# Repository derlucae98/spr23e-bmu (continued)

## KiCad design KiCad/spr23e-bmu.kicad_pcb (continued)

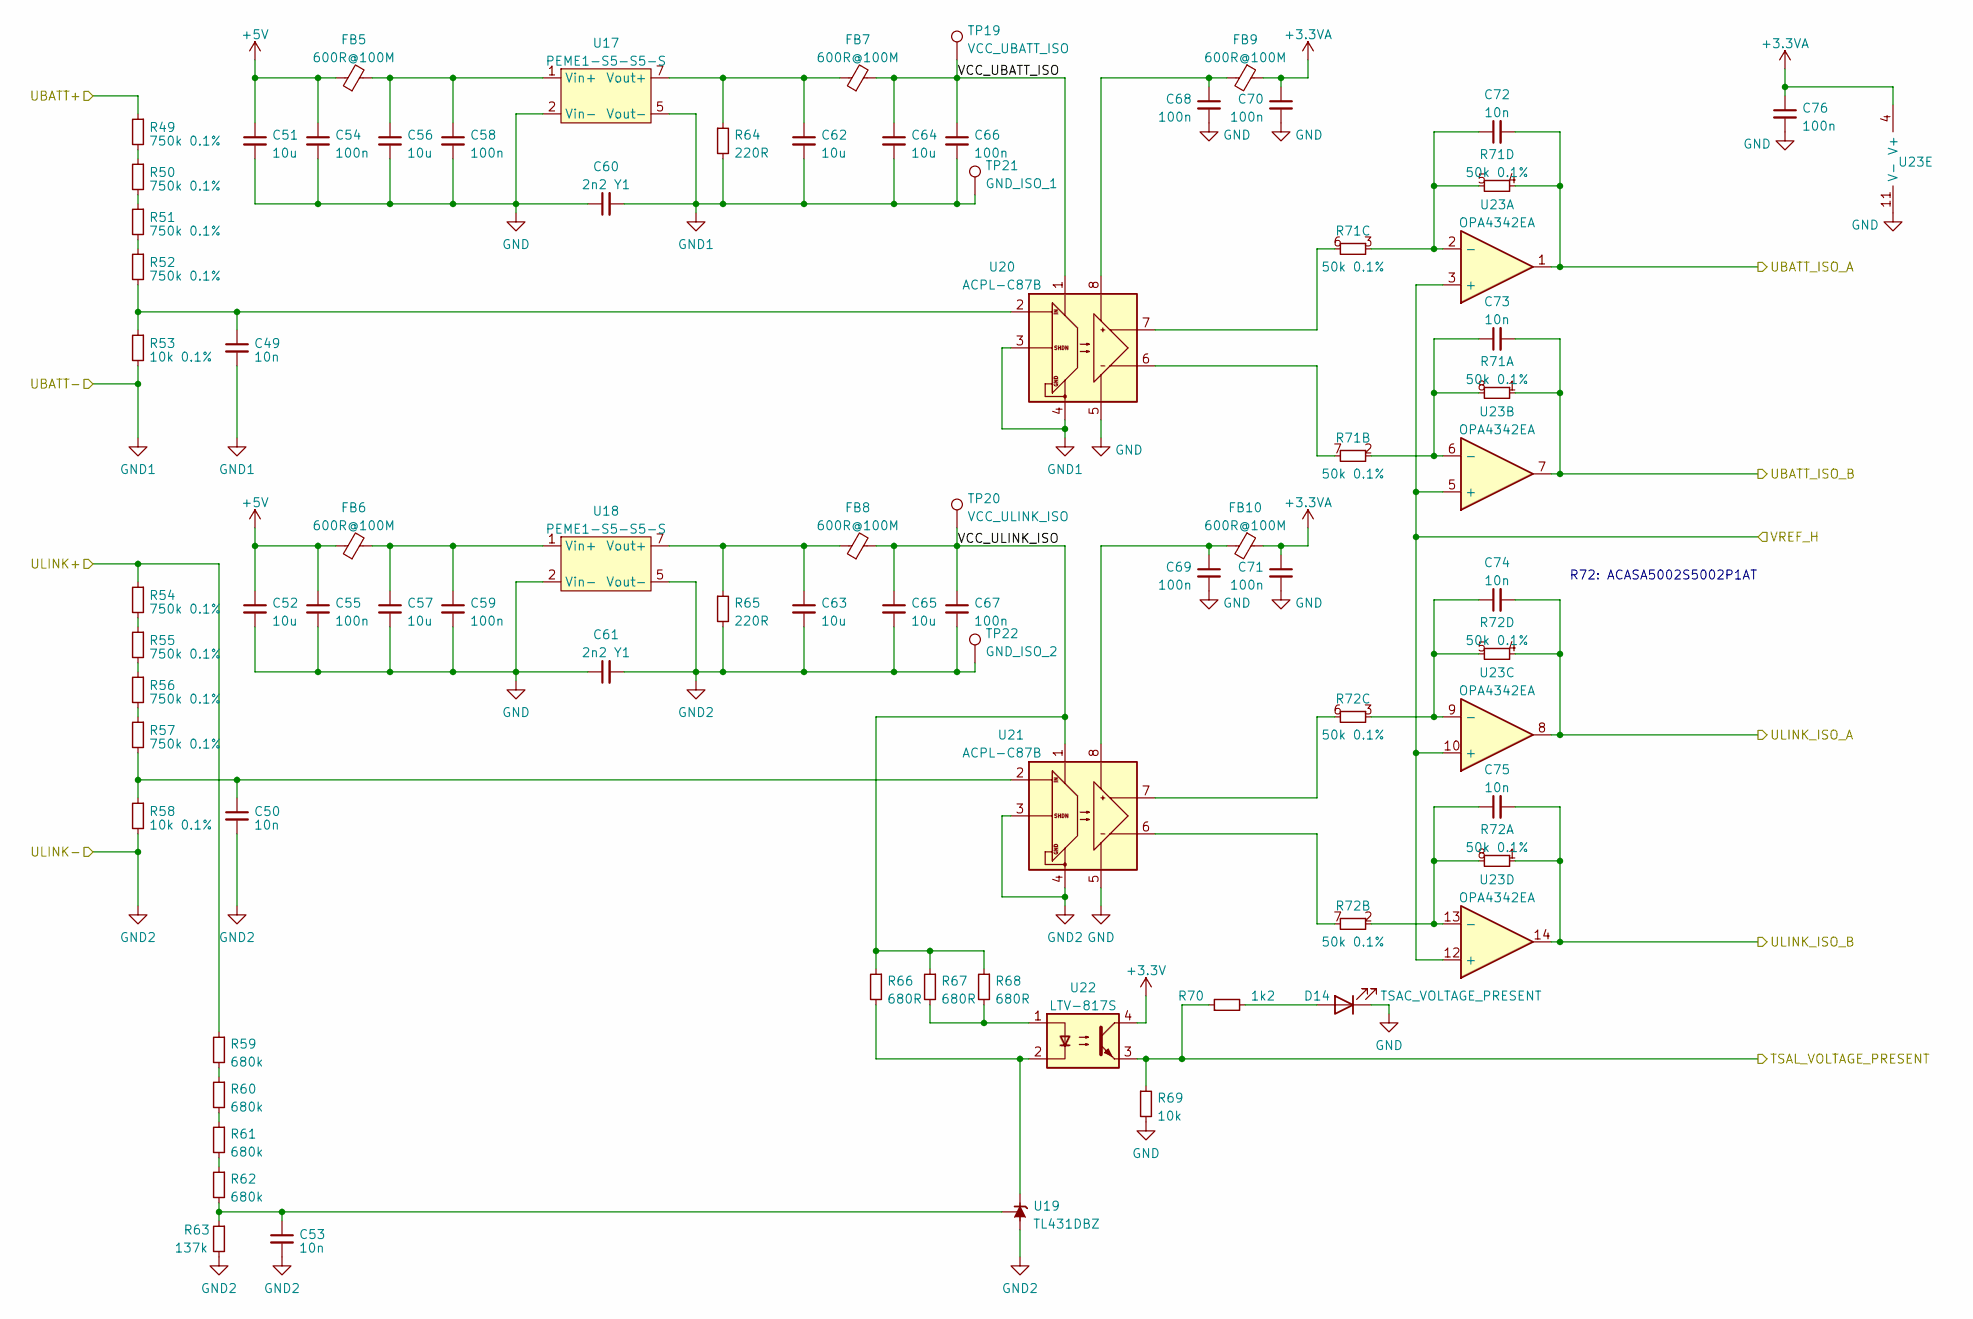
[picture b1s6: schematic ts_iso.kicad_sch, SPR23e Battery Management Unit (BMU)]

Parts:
C49, C50, C53, C72, C73, C74, C75: 10n; C_0603_1608Metric
C51, C52, C56, C57, C62, C63, C64, C65: 10u; C_1206_3216Metric
C54, C55, C58, C59, C66, C67, C68, C69, C70, C71, C76: 100n; C_0603_1608Metric
C60, C61: 2n2 Y1; C_Rect_L13.0mm_W4.0mm_P10.00mm_FKS3_FKP3_MKS4
D14: TSAC_VOLTAGE_PRESENT; LED_0603_1608Metric
FB5, FB6, FB7, FB8, FB9, FB10: 600R@100M; L_0603_1608Metric
R49, R50, R51, R52, R54, R55, R56, R57: 750k 0.1%; R_1206_3216Metric
R53, R58: 10k 0.1%; R_0603_1608Metric
R59, R60, R61, R62: 680k; R_1206_3216Metric
R63: 137k; R_0603_1608Metric
R64, R65: 220R; R_1210_3225Metric
R66, R67, R68: 680R; R_0603_1608Metric
R69: 10k; R_0603_1608Metric
R70: 1k2; R_0603_1608Metric
R71, R72: 50k 0.1%; R_Array_Convex_4x0603
TP19: VCC_UBATT_ISO; TestPoint_Pad_D1.5mm
TP20: VCC_ULINK_ISO; TestPoint_Pad_D1.5mm
TP21: GND_ISO_1; TestPoint_Pad_D1.5mm
TP22: GND_ISO_2; TestPoint_Pad_D1.5mm
U17, U18: PEME1-S5-S5-S; PEME1
U19: TL431DBZ; SOT-23
U20, U21: ACPL-C87B; SSO-8_6.8x5.9mm_P1.27mm_Clearance8mm
U22: LTV-817S; SMDIP-4_W9.53mm
U23: OPA4342EA; TSSOP-14_4.4x5mm_P0.65mm

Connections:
+3.3V: U22.4; also elsewhere on the board
+3.3VA: C70.1, C71.1, C76.1, FB9.1, FB10.1, U23.4 (V+); also elsewhere on the board
+5V: C51.1, C52.1, C54.1, C55.1, FB5.1, FB6.1; also elsewhere on the board
/ADC/UBATT_ISO_A: C72.2, R71.4, U23.1; also elsewhere on the board
/ADC/UBATT_ISO_B: C73.2, R71.1, U23.7; also elsewhere on the board
/ADC/ULINK_ISO_A: C74.2, R72.4, U23.8; also elsewhere on the board
/ADC/ULINK_ISO_B: C75.2, R72.1, U23.14; also elsewhere on the board
/ADC/VREF_H: U23.3 (+), U23.5 (+), U23.10 (+), U23.12 (+); also elsewhere on the board
/AMS-Master/TSAC_VOLTAGE_PRESENT: R69.1, R70.1, U22.3; also elsewhere on the board
/TS_ISO/VCC_UBATT_ISO: C64.1, C66.1, FB7.2, TP19.1, U20.1 (VDD1)
/TS_ISO/VCC_ULINK_ISO: C65.1, C67.1, FB8.2, R66.1, R67.1, R68.1, TP20.1, U21.1 (VDD1)
/UBATT+: R49.1; also elsewhere on the board
/ULINK+: R54.1, R59.1; also elsewhere on the board
GND: C51.2, C52.2, C54.2, C55.2, C56.2, C57.2, C58.2, C59.2, C60.1, C61.1, C68.2, C69.2, C70.2, C71.2, C76.2, D14.1 (K), R69.2, U17.2 (Vin-), U18.2 (Vin-), U20.5 (GND2), U21.5 (GND2), U23.11 (V-); also elsewhere on the board
GND1: C49.2, C60.2, C62.2, C64.2, C66.2, R53.2, R64.2, TP21.1, U17.5 (Vout-), U20.3 (IN-), U20.4 (GND1); also elsewhere on the board
GND2: C50.2, C53.2, C61.2, C63.2, C65.2, C67.2, R58.2, R63.2, R65.2, TP22.1, U18.5 (Vout-), U19.3 (A), U21.3 (IN-), U21.4 (GND1); also elsewhere on the board
unnamed: D14.2 (A), R70.2
unnamed: R49.2, R50.1
unnamed: R50.2, R51.1
unnamed: R51.2, R52.1
unnamed: R54.2, R55.1
unnamed: R55.2, R56.1
unnamed: R56.2, R57.1
unnamed: R59.2, R60.1
unnamed: R60.2, R61.1
unnamed: R61.2, R62.1
unnamed: R67.2, R68.2, U22.1
unnamed: C56.1, C58.1, FB5.2, U17.1 (Vin+)
unnamed: C62.1, FB7.1, R64.1, U17.7 (Vout+)
unnamed: C57.1, C59.1, FB6.2, U18.1 (Vin+)
unnamed: C63.1, FB8.1, R65.1, U18.7 (Vout+)
unnamed: R66.2, U19.1 (K), U22.2
unnamed: C53.1, R62.2, R63.1, U19.2 (REF)
unnamed: C49.1, R52.2, R53.1, U20.2 (IN)
unnamed: R71.6, U20.7 (OUT+)
unnamed: R71.7, U20.6 (OUT-)
unnamed: C68.1, FB9.2, U20.8 (VDD2)
unnamed: C50.1, R57.2, R58.1, U21.2 (IN)
unnamed: R72.6, U21.7 (OUT+)
unnamed: R72.7, U21.6 (OUT-)
unnamed: C69.1, FB10.2, U21.8 (VDD2)
unnamed: C72.1, R71.3, R71.5, U23.2 (-)
unnamed: C73.1, R71.2, R71.8, U23.6 (-)
unnamed: C74.1, R72.3, R72.5, U23.9 (-)
unnamed: C75.1, R72.2, R72.8, U23.13 (-)

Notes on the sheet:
R72: ACASA5002S5002P1AT

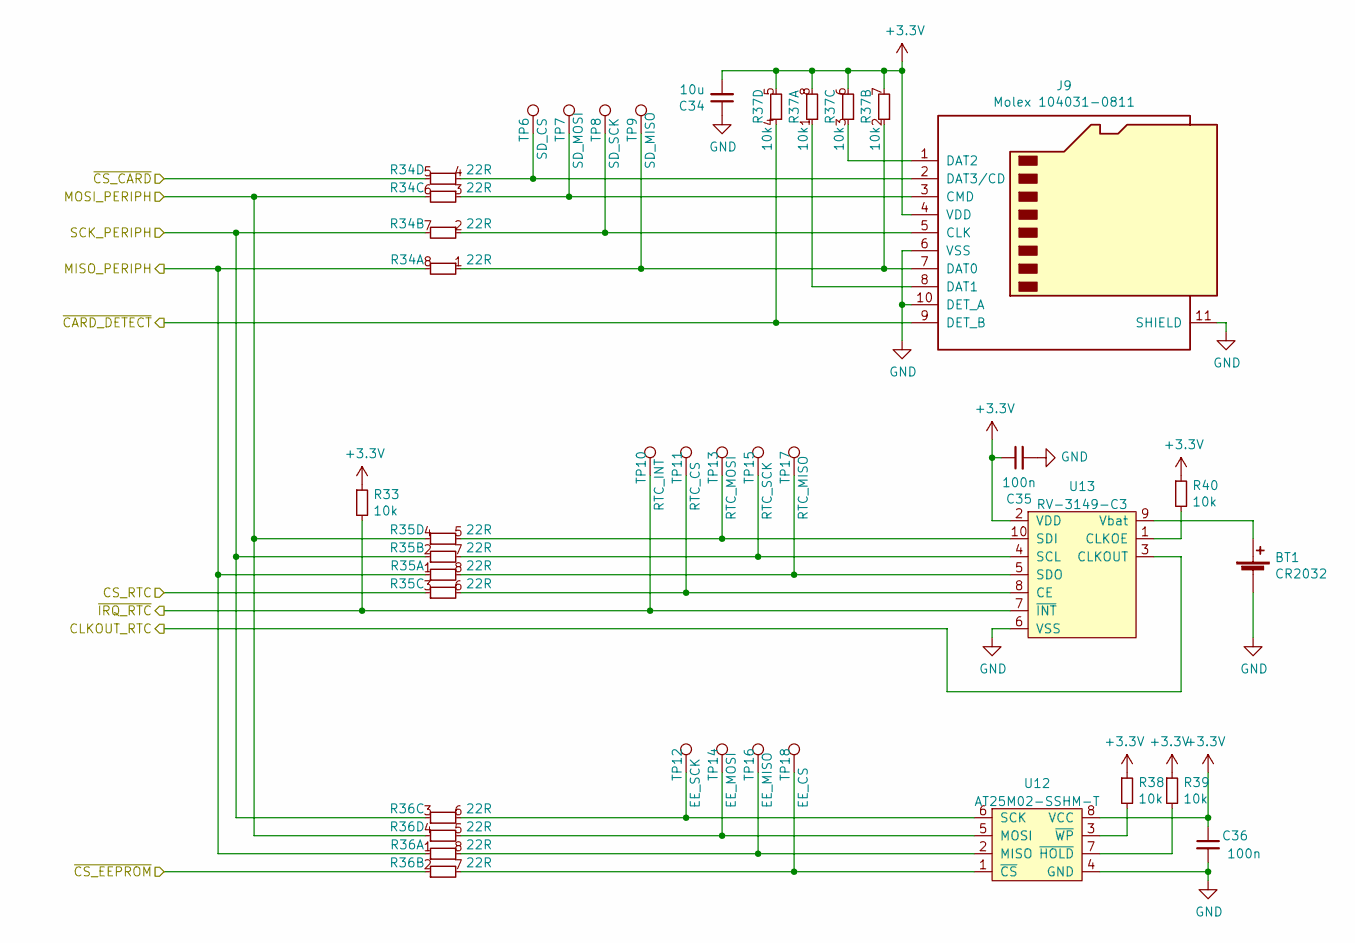
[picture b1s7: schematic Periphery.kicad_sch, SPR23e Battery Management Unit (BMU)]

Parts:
BT1: CR2032; WA-BCPH_79527141
C34: 10u; C_1206_3216Metric
C35, C36: 100n; C_0603_1608Metric
J9: Molex 104031-0811; microSD_HC_Molex_104031-0811
R33, R38, R39, R40: 10k; R_0603_1608Metric
R34, R35, R36: 22R; R_Array_Convex_4x0603
R37: 10k; R_Array_Convex_4x0603
TP6: SD_CS; TestPoint_Pad_D1.5mm
TP7: SD_MOSI; TestPoint_Pad_D1.5mm
TP8: SD_SCK; TestPoint_Pad_D1.5mm
TP9: SD_MISO; TestPoint_Pad_D1.5mm
TP10: RTC_INT; TestPoint_Pad_D1.5mm
TP11: RTC_CS; TestPoint_Pad_D1.5mm
TP12: EE_SCK; TestPoint_Pad_D1.5mm
TP13: RTC_MOSI; TestPoint_Pad_D1.5mm
TP14: EE_MOSI; TestPoint_Pad_D1.5mm
TP15: RTC_SCK; TestPoint_Pad_D1.5mm
TP16: EE_MISO; TestPoint_Pad_D1.5mm
TP17: RTC_MISO; TestPoint_Pad_D1.5mm
TP18: EE_CS; TestPoint_Pad_D1.5mm
U12: AT25M02-SSHM-T; SOIC-8_3.9x4.9mm_P1.27mm
U13: RV-3149-C3; RTC_SMD_MicroCrystal_C3_2.5x3.7mm

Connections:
+3.3V: C34.2, C35.1, C36.1, J9.4 (VDD), R33.1, R37.5, R37.6, R37.7, R37.8, R38.1, R39.1, R40.1, U12.8 (VCC), U13.2 (VDD); also elsewhere on the board
/AMS-Master/CLKOUT_RTC: U13.3 (CLKOUT); also elsewhere on the board
/AMS-Master/CS_RTC: R35.3; also elsewhere on the board
/AMS-Master/SPI2_MISO: R34.8, R35.1, R36.1; also elsewhere on the board
/AMS-Master/SPI2_MOSI: R34.6, R35.4, R36.4; also elsewhere on the board
/AMS-Master/SPI2_SCK: R34.7, R35.2, R36.3; also elsewhere on the board
/AMS-Master/~CARD_DETECT: J9.9 (DET_B), R37.4; also elsewhere on the board
/AMS-Master/~CS_CARD: R34.5; also elsewhere on the board
/AMS-Master/~CS_EEPROM: R36.2; also elsewhere on the board
/AMS-Master/~IRQ_RTC: R33.2, TP10.1, U13.7 (~INT); also elsewhere on the board
GND: BT1.2 (-), C34.1, C35.2, C36.2, J9.6 (VSS), J9.10 (DET_A), J9.11 (SHIELD), U12.4 (GND), U13.6 (VSS); also elsewhere on the board
unnamed: BT1.1 (+), U13.9 (Vbat)
unnamed: J9.5 (CLK), R34.2, TP8.1
unnamed: J9.3 (CMD), R34.3, TP7.1
unnamed: J9.7 (DAT0), R34.1, R37.2, TP9.1
unnamed: J9.8 (DAT1), R37.1
unnamed: J9.1 (DAT2), R37.3
unnamed: J9.2 (DAT3/CD), R34.4, TP6.1
unnamed: R36.8, TP16.1, U12.2 (MISO)
unnamed: R36.5, TP14.1, U12.5 (MOSI)
unnamed: R36.6, TP12.1, U12.6 (SCK)
unnamed: R36.7, TP18.1, U12.1 (~CS)
unnamed: R39.2, U12.7 (~HOLD)
unnamed: R38.2, U12.3 (~WP)
unnamed: R35.6, TP11.1, U13.8 (CE)
unnamed: R40.2, U13.1 (CLKOE)
unnamed: R35.7, TP15.1, U13.4 (SCL)
unnamed: R35.5, TP13.1, U13.10 (SDI)
unnamed: R35.8, TP17.1, U13.5 (SDO)

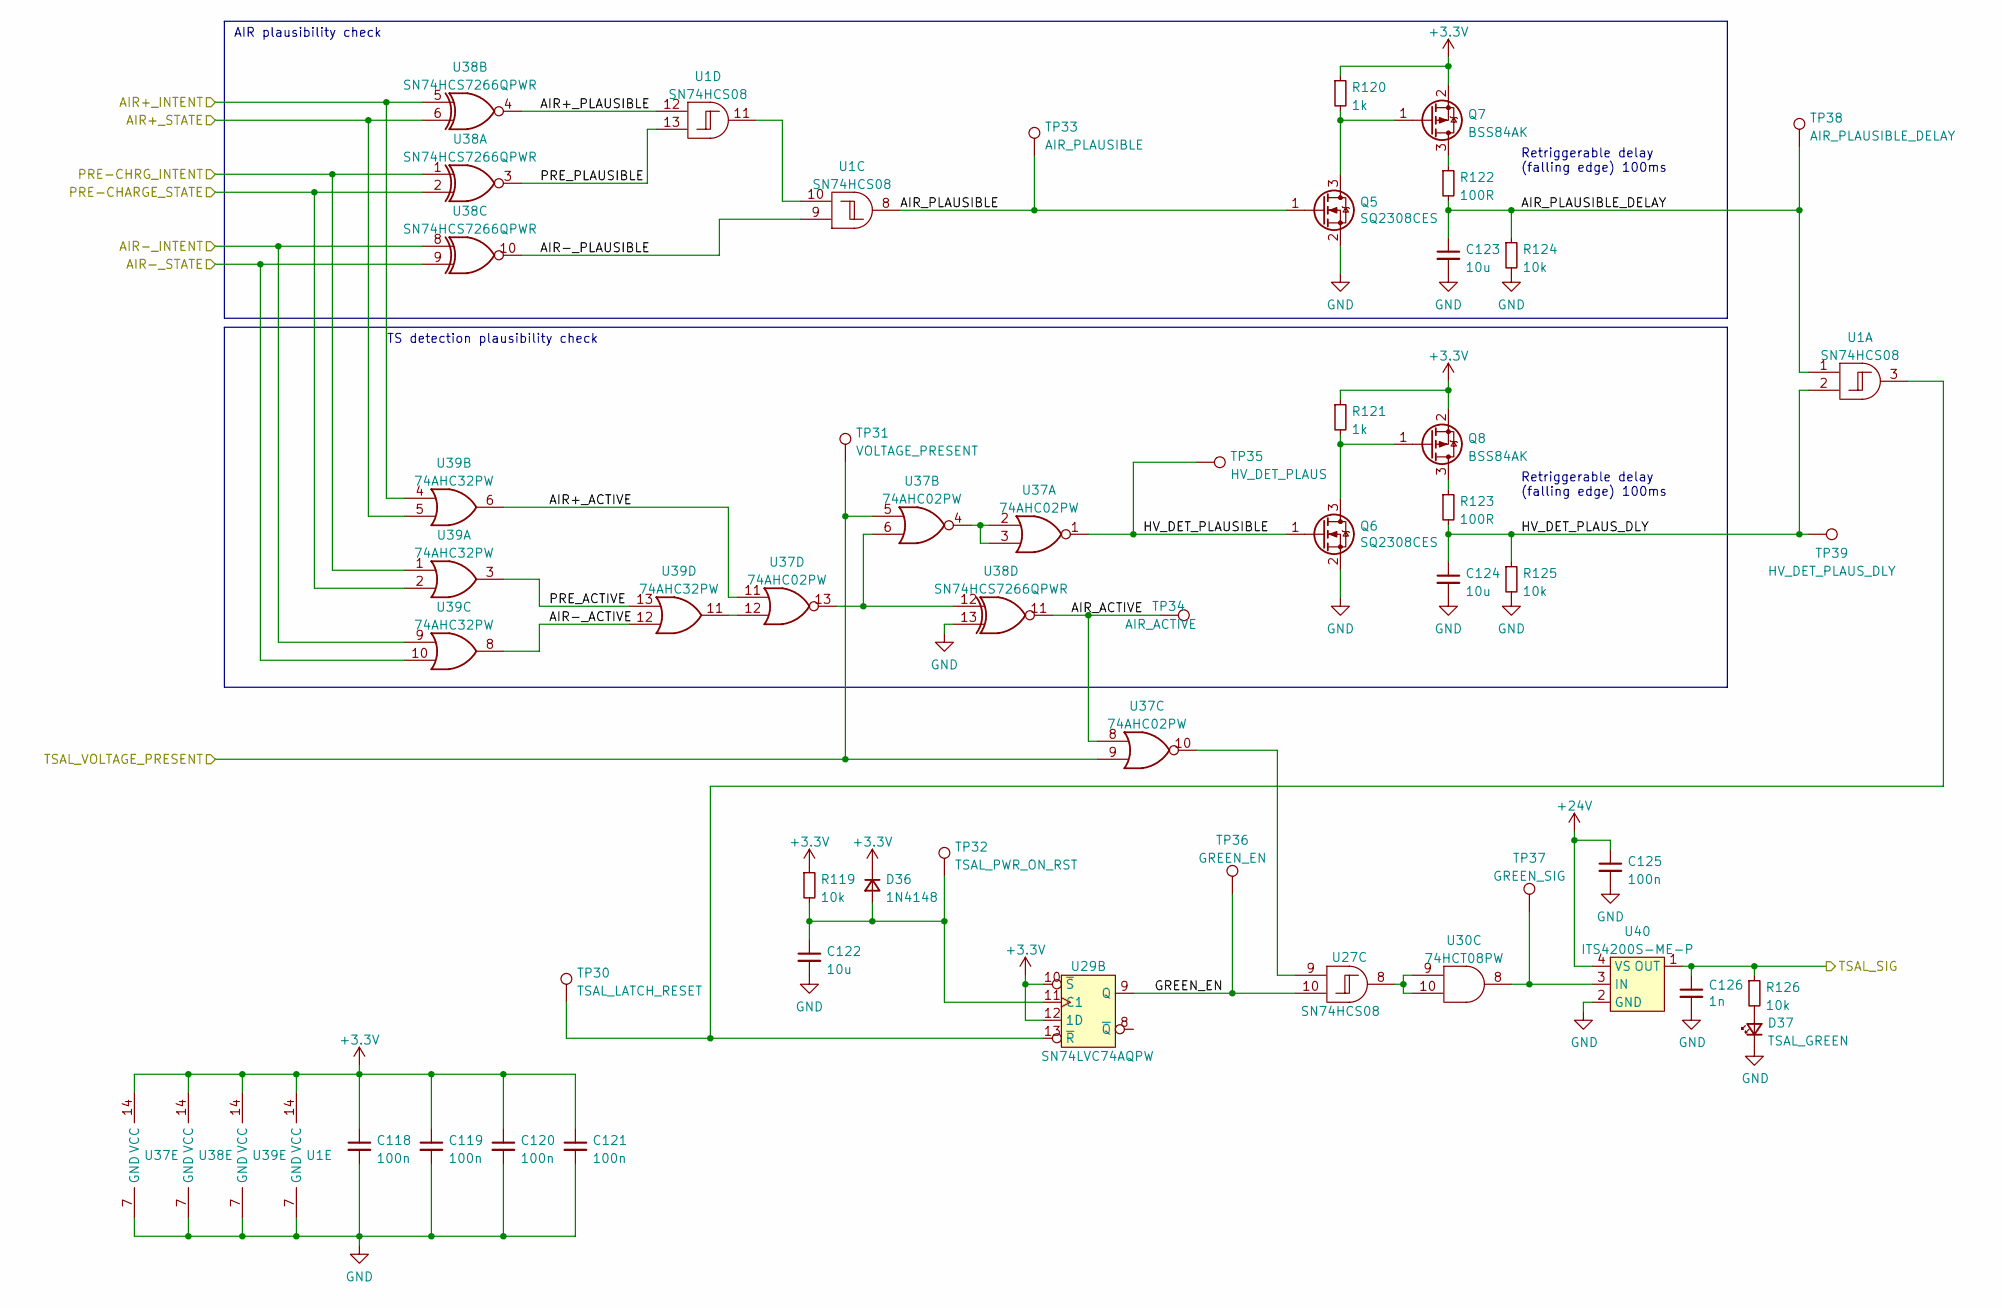
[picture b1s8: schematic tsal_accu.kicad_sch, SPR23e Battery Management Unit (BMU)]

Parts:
C118, C119, C120, C121, C125: 100n; C_0603_1608Metric
C122, C123, C124: 10u; C_1206_3216Metric
C126: 1n; C_0603_1608Metric
D36: 1N4148; D_SOD-123
D37: TSAL_GREEN; LED_0603_1608Metric
Q5, Q6: SQ2308CES; SOT-23
Q7, Q8: BSS84AK; SOT-23
R119, R124, R125, R126: 10k; R_0603_1608Metric
R120, R121: 1k; R_0603_1608Metric
R122, R123: 100R; R_0603_1608Metric
TP30: TSAL_LATCH_RESET; TestPoint_Pad_D1.5mm
TP31: VOLTAGE_PRESENT; TestPoint_Pad_D1.5mm
TP32: TSAL_PWR_ON_RST; TestPoint_Pad_D1.5mm
TP33: AIR_PLAUSIBLE; TestPoint_Pad_D1.5mm
TP34: AIR_ACTIVE; TestPoint_Pad_D1.5mm
TP35: HV_DET_PLAUS; TestPoint_Pad_D1.5mm
TP36: GREEN_EN; TestPoint_Pad_D1.5mm
TP37: GREEN_SIG; TestPoint_Pad_D1.5mm
TP38: AIR_PLAUSIBLE_DELAY; TestPoint_Pad_D1.5mm
TP39: HV_DET_PLAUS_DLY; TestPoint_Pad_D1.5mm
U1, U27: SN74HCS08; TSSOP-14_4.4x5mm_P0.65mm
U29: SN74LVC74AQPW; TSSOP-14_4.4x5mm_P0.65mm
U30: 74HCT08PW; TSSOP-14_4.4x5mm_P0.65mm
U37: 74AHC02PW; TSSOP-14_4.4x5mm_P0.65mm
U38: SN74HCS7266QPWR; TSSOP-14_4.4x5mm_P0.65mm
U39: 74AHC32PW; TSSOP-14_4.4x5mm_P0.65mm
U40: ITS4200S-ME-P; SOT-223

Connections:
+3.3V: C118.1, C119.1, C120.1, C121.1, D36.1 (K), Q7.2 (S), Q8.2 (S), R119.1, R120.1, R121.1, U1.14 (VCC), U29.10 (~S), U29.12 (1D), U37.14 (VCC), U38.14 (VCC), U39.14 (VCC); also elsewhere on the board
+24V: C125.1, U40.4 (VS); also elsewhere on the board
/AMS-Master/AIR+_INTENT: U38.5, U39.4; also elsewhere on the board
/AMS-Master/AIR+_STATE: U38.6, U39.5; also elsewhere on the board
/AMS-Master/AIR-_INTENT: U38.8, U39.9; also elsewhere on the board
/AMS-Master/AIR-_STATE: U38.9, U39.10; also elsewhere on the board
/AMS-Master/PRE-CHARGE_STATE: U38.2, U39.2; also elsewhere on the board
/AMS-Master/PRE_INTENT: U38.1, U39.1; also elsewhere on the board
/AMS-Master/TSAC_VOLTAGE_PRESENT: TP31.1, U37.5, U37.9; also elsewhere on the board
/TSAL/AIR+_ACTIVE: U37.11, U39.6
/TSAL/AIR+_PLAUSIBLE: U1.12, U38.4
/TSAL/AIR-_ACTIVE: U39.8, U39.12
/TSAL/AIR-_PLAUSIBLE: U1.9, U38.10
/TSAL/AIR_ACTIVE: TP34.1, U37.8, U38.11
/TSAL/AIR_PLAUSIBLE: Q5.1 (G), TP33.1, U1.8
/TSAL/AIR_PLAUSIBLE_DELAY: C123.1, R122.2, R124.1, TP38.1, U1.1
/TSAL/GREEN_EN: TP36.1, U27.10, U29.9 (Q)
/TSAL/HV_DET_PLAUSIBLE: Q6.1 (G), TP35.1, U37.1
/TSAL/HV_DET_PLAUS_DLY: C124.1, R123.2, R125.1, TP39.1, U1.2
/TSAL/PRE_ACTIVE: U39.3, U39.13
/TSAL/PRE_PLAUSIBLE: U1.13, U38.3
/TSAL_SIG: C126.1, R126.1, U40.1 (OUT); also elsewhere on the board
GND: C118.2, C119.2, C120.2, C121.2, C122.2, C123.2, C124.2, C125.2, C126.2, D37.1 (K), Q5.2 (S), Q6.2 (S), R124.2, R125.2, U1.7 (GND), U37.7 (GND), U38.7 (GND), U38.13, U39.7 (GND), U40.2 (GND); also elsewhere on the board
unnamed: C122.1, D36.2 (A), R119.2, TP32.1, U29.11 (C1)
unnamed: D37.2 (A), R126.2
unnamed: Q5.3 (D), Q7.1 (G), R120.2
unnamed: Q6.3 (D), Q8.1 (G), R121.2
unnamed: Q7.3 (D), R122.1
unnamed: Q8.3 (D), R123.1
unnamed: U1.10, U1.11
unnamed: U27.8, U30.9, U30.10
unnamed: U27.9, U37.10
unnamed: TP30.1, U1.3, U29.13 (~R)
unnamed: U37.2, U37.3, U37.4
unnamed: U37.12, U39.11
unnamed: U37.6, U37.13, U38.12
unnamed: TP37.1, U30.8, U40.3 (IN)

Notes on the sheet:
AIR plausibility check
Retriggerable delay (falling edge) 100ms
TS detection plausibility check

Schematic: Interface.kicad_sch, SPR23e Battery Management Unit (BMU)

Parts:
C37, C38, C39, C40, C41, C42: 100n; C_0603_1608Metric
C43, C46: 10n; C_0603_1608Metric
C44, C45, C47, C48: 100p; C_0603_1608Metric
D12, D13: NUP2105L; SOT-23
FL1, FL2: B82793C0475N265; B82793C0
JP1, JP2: Termination; SolderJumper-2_P1.3mm_Open_Pad1.0x1.5mm
R41: 22R; R_Array_Convex_4x0603
R42: 1k; R_0603_1608Metric
R43: 2k8; R_0603_1608Metric
R44: 1k21; R_0603_1608Metric
R45, R46: 120R; R_1206_3216Metric
R47, R48: 51R; R_0603_1608Metric
TR1: SM91502AL
U14, U15: SN65HVDA540; SOIC-8_3.9x4.9mm_P1.27mm
U16: LTC6820; MSOP-16_3x4.039mm_P0.5mm

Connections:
+3.3V: C38.1, C40.1, C41.1, C42.1, R42.1, U14.5 (VIO), U15.5 (VIO), U16.1 (EN), U16.6 (VDDS), U16.7 (POL), U16.8 (PHA), U16.9 (VDD), U16.12 (MSTR); also elsewhere on the board
+5V: C37.1, C39.1, U14.3 (VCC), U15.3 (VCC); also elsewhere on the board
/AMS-Master/CAN0_RX: U15.4 (RXD); also elsewhere on the board
/AMS-Master/CAN0_TX: U15.1 (TXD); also elsewhere on the board
/AMS-Master/CAN1_RX: U14.4 (RXD); also elsewhere on the board
/AMS-Master/CAN1_TX: U14.1 (TXD); also elsewhere on the board
/AMS-Master/MISO_SLAVES: R41.2; also elsewhere on the board
/AMS-Master/MOSI_SLAVES: R41.1; also elsewhere on the board
/AMS-Master/SCK_SLAVES: R41.3; also elsewhere on the board
/AMS-Master/~CS_SLAVES: R41.4; also elsewhere on the board
/CAN_H_DIAG: FL1.2; also elsewhere on the board
/CAN_H_VEHIC: FL2.2; also elsewhere on the board
/CAN_L_DIAG: FL1.4; also elsewhere on the board
/CAN_L_VEHIC: FL2.4; also elsewhere on the board
/ISO_A: TR1.6; also elsewhere on the board
/ISO_B: TR1.4; also elsewhere on the board
GND: C37.2, C38.2, C39.2, C40.2, C41.2, C42.2, C43.1, C44.1, C45.1, C46.1, C47.1, C48.1, D12.3 (A), D13.3 (A), R44.1, U14.2 (GND), U14.8 (STB), U15.2 (GND), U15.8 (STB), U16.13 (SLOW), U16.14 (GND); also elsewhere on the board
unnamed: C43.2, R47.1, R48.1
unnamed: C46.2, TR1.2
unnamed: C47.2, D12.2 (K), FL1.1, JP1.1 (A), U14.7 (CANH)
unnamed: JP1.2 (B), R45.1
unnamed: C48.2, D13.2 (K), FL2.1, JP2.1 (A), U15.7 (CANH)
unnamed: JP2.2 (B), R46.1
unnamed: C44.2, D12.1 (K), FL1.3, R45.2, U14.6 (CANL)
unnamed: C45.2, D13.1 (K), FL2.3, R46.2, U15.6 (CANL)
unnamed: R43.2, U16.16 (IBIAS)
unnamed: R43.1, R44.2, U16.15 (ICMP)
unnamed: R47.2, TR1.3, U16.10 (IM)
unnamed: R48.2, TR1.1, U16.11 (IP)
unnamed: R41.7, R42.2, U16.3 (MISO)
unnamed: R41.8, U16.2 (MOSI)
unnamed: R41.6, U16.4 (SCK)
unnamed: R41.5, U16.5 (~CS)

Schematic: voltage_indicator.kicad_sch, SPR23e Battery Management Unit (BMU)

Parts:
C103: 10n; C_0603_1608Metric
C104, C110: 100n 1kV; C_1812_4532Metric
C105, C114, C116, C117: 100n; C_0603_1608Metric
C106, C107, C108, C109: 10u; CP_Radial_D10.0mm_P5.00mm
C111: 1n; C_0603_1608Metric
C112: 220n; C_0603_1608Metric
C113: 2u2; C_0805_2012Metric
C115: 330u; CP_Radial_D10.0mm_P5.00mm
D30, D31, D34, D35: US1M; D_SMA
D32: ZD12V; D_SOD-123
D33: 1N4148; D_SOD-123
L3: 100u; L_Taiyo-Yuden_MD-3030
L4, L5: 3m3; L_Wuerth_WE-PD-Typ-LS
Q4: BC857C; SOT-23
R95, R96, R97, R98, R100, R101, R102, R103, R104, R105, R106, R107, R109, R110, R111, R112: 470k; R_1206_3216Metric
R99: 13k7; R_0603_1608Metric
R108: 1M; R_0603_1608Metric
R113: 62k; R_0603_1608Metric
R114: 3k3; R_0603_1608Metric
R115: 2k8; R_0603_1608Metric
R116, R117: 10k; R_0603_1608Metric
R118: 180R; R_0603_1608Metric
U34: LT6700-1; SOT-23-6
U35: VIPER012BHSTR; SSOP-10_3.9x4.9mm_P1.00mm
U36: PEME1-S24-S5-S; PEME1

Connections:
/HVI+: R118.2; also elsewhere on the board
/HVI/DRAIN: C108.1, C110.1, L3.2, R109.1, U35.6 (DRAIN), U35.7 (DRAIN), U35.8 (DRAIN), U35.9 (DRAIN), U35.10 (DRAIN)
/HVI/SW: C112.2, C113.2, C114.2, D34.1 (K), L4.1, R114.2, R115.2, U35.1 (GND), U35.3 (DIS)
/PRE-CHRG: D31.2 (A); also elsewhere on the board
/ULINK+: D30.2 (A); also elsewhere on the board
GND: C117.2, U36.5 (Vout-); also elsewhere on the board
GND2: C103.2, C104.2, C105.2, C107.2, C109.2, C110.2, C115.2, C116.2, D32.2 (A), D34.2 (A), R99.2, R107.2, R112.2, U34.2 (GND), U34.3 (+INA), U36.2 (Vin-); also elsewhere on the board
unnamed: C106.2, C107.1, R105.2, R106.1
unnamed: C108.2, C109.1, R110.2, R111.1
unnamed: C111.2, R115.1
unnamed: C104.1, C106.1, D30.1 (K), D31.1 (K), L3.1, R95.1, R100.1, R104.1
unnamed: C105.1, D32.1 (K), R103.2, U34.5 (Vs)
unnamed: C112.1, D33.2 (A), D35.1 (K), R113.1
unnamed: C113.1, C114.1, D33.1 (K), U35.2 (VCC)
unnamed: C115.1, D35.2 (A), L5.2, Q4.2 (E), R116.1
unnamed: L4.2, L5.1
unnamed: Q4.1 (B), R116.2, R117.1
unnamed: C116.1, Q4.3 (C), R108.2, U36.1 (Vin+)
unnamed: R95.2, R96.1
unnamed: R96.2, R97.1
unnamed: R97.2, R98.1
unnamed: R100.2, R101.1
unnamed: R101.2, R102.1
unnamed: R102.2, R103.1
unnamed: R104.2, R105.1
unnamed: R106.2, R107.1
unnamed: R109.2, R110.1
unnamed: R111.2, R112.1
unnamed: C103.1, R98.2, R99.1, R108.1, U34.4 (-INB)
unnamed: R117.2, U34.6 (OUTB)
unnamed: C111.1, U35.5 (COMP)
unnamed: R113.2, R114.1, U35.4 (FB)
unnamed: C117.1, R118.1, U36.7 (Vout+)

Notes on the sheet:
26uA @ 50V 320uA @ 600V Is = 15.5uA @ 12V Iz(50V) = 26uA - 15.5uA = 10.5uA Pv,max = 0.2W -> 0.05W/Resistor
U35 is a regulated buck converter, which converts the TS voltage down to 24V. It operates in a range of 50V to 600V and is not galvanically isolated. Below 50V, the output is unstable and starts to pulse at a slow rate. U36 is a galvanically isolated DCDC converter, which isolates the LED supply fr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

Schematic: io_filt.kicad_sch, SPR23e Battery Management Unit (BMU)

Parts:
C84, C85, C86, C92, C93, C94, C95, C97, C98, C99: 100n; C_0603_1608Metric
C87, C88, C89, C90, C91, C100, C101, C102: 1n; C_0603_1608Metric
C96: 330u; CP_Radial_D10.0mm_P5.00mm
D18: US1M; D_SMA
D19, D20, D21, D22, D23, D24, D25, D26: ZD3V3; D_SOD-123
D27: AIR+; LED_0603_1608Metric
D28: AIR-; LED_0603_1608Metric
D29: PRE-CHARGE; LED_0603_1608Metric
L2: 4u7; L_1206_3216Metric
R74, R75, R76, R77, R78: 2k2; R_1210_3225Metric
R79, R80, R82, R83, R84, R85, R86, R87, R88, R89, R90, R91: 10k; R_0603_1608Metric
R81: 10k; R_Array_Convex_4x0603
R92, R93, R94: 1k2; R_0603_1608Metric
U27: SN74HCS08; TSSOP-14_4.4x5mm_P0.65mm
U28, U29: SN74LVC74AQPW; TSSOP-14_4.4x5mm_P0.65mm
U30: 74HCT08PW; TSSOP-14_4.4x5mm_P0.65mm
U31, U32, U33: ITS4200S-ME-P; SOT-223

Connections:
+3.3V: C84.1, C85.1, C86.1, U27.14 (VCC), U28.2 (1D), U28.4 (~S), U28.10 (~S), U28.12 (1D), U28.14 (VCC), U29.2 (1D), U29.4 (~S), U29.14 (VCC); also elsewhere on the board
+5V: C95.1, U30.14 (VCC); also elsewhere on the board
/AIR+: C100.1, U31.1 (OUT); also elsewhere on the board
/AIR+_STATE: R74.2, R83.1; also elsewhere on the board
/AIR-: C101.1, U32.1 (OUT); also elsewhere on the board
/AIR-_STATE: R75.2, R84.1; also elsewhere on the board
/AMS-Master/AIR+_INTENT: R92.1, U28.5 (Q), U30.12, U30.13; also elsewhere on the board
/AMS-Master/AIR+_SET: R81.2, U28.3 (C1); also elsewhere on the board
/AMS-Master/AIR+_STATE: C87.1, D19.1 (K), R83.2; also elsewhere on the board
/AMS-Master/AIR+_~RESET: R81.1, U27.2; also elsewhere on the board
/AMS-Master/AIR-_INTENT: R93.1, U28.9 (Q), U30.1, U30.2; also elsewhere on the board
/AMS-Master/AIR-_SET: R81.4, U28.11 (C1); also elsewhere on the board
/AMS-Master/AIR-_STATE: C88.1, D20.1 (K), R84.2; also elsewhere on the board
/AMS-Master/AIR-_~RESET: R81.3, U27.5; also elsewhere on the board
/AMS-Master/IMD_MEAS: C91.1, D23.1 (K), R87.2; also elsewhere on the board
/AMS-Master/IMD_STATUS: C90.1, D22.1 (K), R86.2; also elsewhere on the board
/AMS-Master/PRE-CHARGE_SET: R82.2, U29.3 (C1); also elsewhere on the board
/AMS-Master/PRE-CHARGE_STATE: C89.1, D21.1 (K), R85.2; also elsewhere on the board
/AMS-Master/PRE-CHARGE_~RESET: R91.2, U27.13; also elsewhere on the board
/AMS-Master/PRE_INTENT: R94.1, U29.5 (Q), U30.4, U30.5; also elsewhere on the board
/AMS-Master/SC_STATUS: C94.1, D26.1 (K), R90.2, U27.1, U27.4, U27.12; also elsewhere on the board
/AMS_RESET: R80.2, R89.1; also elsewhere on the board
/IMD_MEAS: R78.2, R87.1; also elsewhere on the board
/IMD_RESET: R79.2, R88.1; also elsewhere on the board
/IMD_STATUS: R77.2, R86.1; also elsewhere on the board
/IO_EMI/AMS_RESET_FILT: C93.1, D25.1 (K), R89.2; also elsewhere on the board
/IO_EMI/IMD_RESET_FILT: C92.1, D24.1 (K), R88.2; also elsewhere on the board
/IO_EMI/SC_RET_FILT: C96.1, C97.1, C98.1, C99.1, L2.2, U31.4 (VS), U32.4 (VS), U33.4 (VS)
/PRE-CHARGE: C102.1, U33.1 (OUT); also elsewhere on the board
/PRE-CHARGE_STATE: R76.2, R85.1; also elsewhere on the board
/SC_RETURN: D18.2 (A), R90.1; also elsewhere on the board
GND: C84.2, C85.2, C86.2, C87.2, C88.2, C89.2, C90.2, C91.2, C92.2, C93.2, C94.2, C95.2, C96.2, C97.2, C98.2, C99.2, C100.2, C101.2, C102.2, D19.2 (A), D20.2 (A), D21.2 (A), D22.2 (A), D23.2 (A), D24.2 (A), D25.2 (A), D26.2 (A), D27.1 (K), D28.1 (K), D29.1 (K), R74.1, R75.1, R76.1, R77.1, R78.1, R79.1, R80.1, R81.5, R81.6, R81.7, R81.8, R82.1, R91.1, U27.7 (GND), U28.7 (GND), U29.7 (GND), U30.7 (GND), U31.2 (GND), U32.2 (GND), U33.2 (GND); also elsewhere on the board
unnamed: D18.1 (K), L2.1
unnamed: D27.2 (A), R92.2
unnamed: D28.2 (A), R93.2
unnamed: D29.2 (A), R94.2
unnamed: U27.3, U28.1 (~R)
unnamed: U27.6, U28.13 (~R)
unnamed: U27.11, U29.1 (~R)
unnamed: U30.11, U31.3 (IN)
unnamed: U30.3, U32.3 (IN)
unnamed: U30.6, U33.3 (IN)

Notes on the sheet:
The latches U28 and U29 fix an issue we had in 2022: If the microcontroller crashes while the AIRs are energized, pushing the emergency button will open the AIRs. However, if you release the emergeny button in this scenario, both AIRs will close without pre-charging. This lead to two stuck AIRs. Th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

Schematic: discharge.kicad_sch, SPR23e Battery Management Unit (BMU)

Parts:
C127, C128: 100n; C_0603_1608Metric
C129: 1n; C_0603_1608Metric
U41: 74HCT2G32; VSSOP-8_2.4x2.1mm_P0.5mm
U42: ITS4200S-ME-P; SOT-223

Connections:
+5V: C127.1, U41.8 (VCC); also elsewhere on the board
/AMS-Master/AIR+_INTENT: U41.1; also elsewhere on the board
/AMS-Master/AIR-_INTENT: U41.5; also elsewhere on the board
/AMS-Master/PRE_INTENT: U41.6; also elsewhere on the board
/DISCHARGE: C129.1, U42.1 (OUT); also elsewhere on the board
/SC_RETURN: C128.1, U42.4 (VS); also elsewhere on the board
GND: C127.2, C128.2, C129.2, U41.4 (GND), U42.2 (GND); also elsewhere on the board
unnamed: U41.2, U41.3
unnamed: U41.7, U42.3 (IN)

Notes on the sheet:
The discharge circuit in the inverter is controlled by the shutdown circuit. To ensure that the discharge circuit is still enabled while the shutdown circuit is closed but TS is still off, the intentional states of the AIRs are used. The discharge circuit is disabled as soon as any of the AIRs is a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

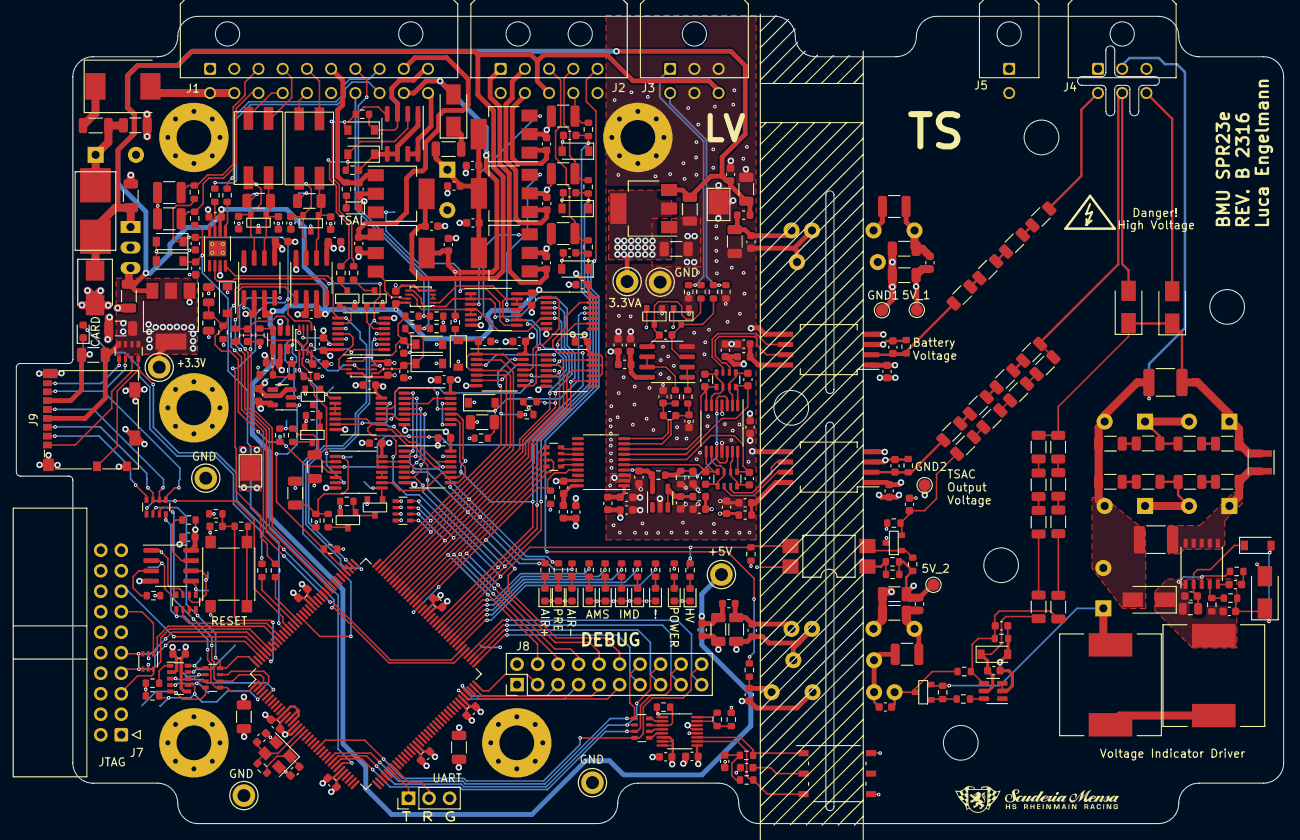
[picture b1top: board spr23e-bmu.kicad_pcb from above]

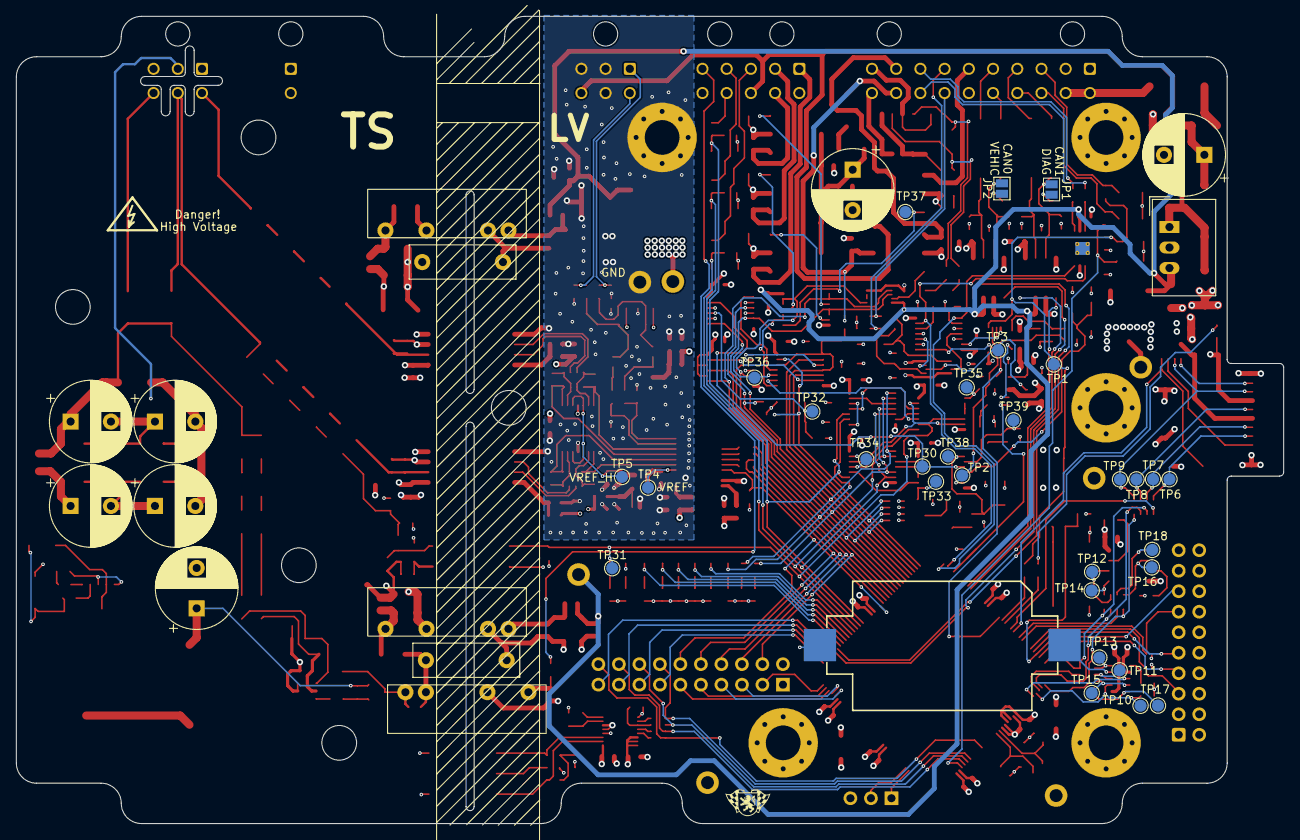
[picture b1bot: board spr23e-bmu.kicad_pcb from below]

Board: 4 copper layers, 157.0 x 100.0 mm, 433 parts (46 on the bottom side), 288 nets.

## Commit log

2023-03-31 Add files
2023-03-31 Update Documentation
2023-04-23 Port to Kicad 7, small changes in auto-reset feature
2023-04-23 Last changes are now documented
2023-07-14 Update KiCad project to newest version
